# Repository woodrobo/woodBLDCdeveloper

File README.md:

# woodBLDCdeveloper
Prototype BLDC motor driver

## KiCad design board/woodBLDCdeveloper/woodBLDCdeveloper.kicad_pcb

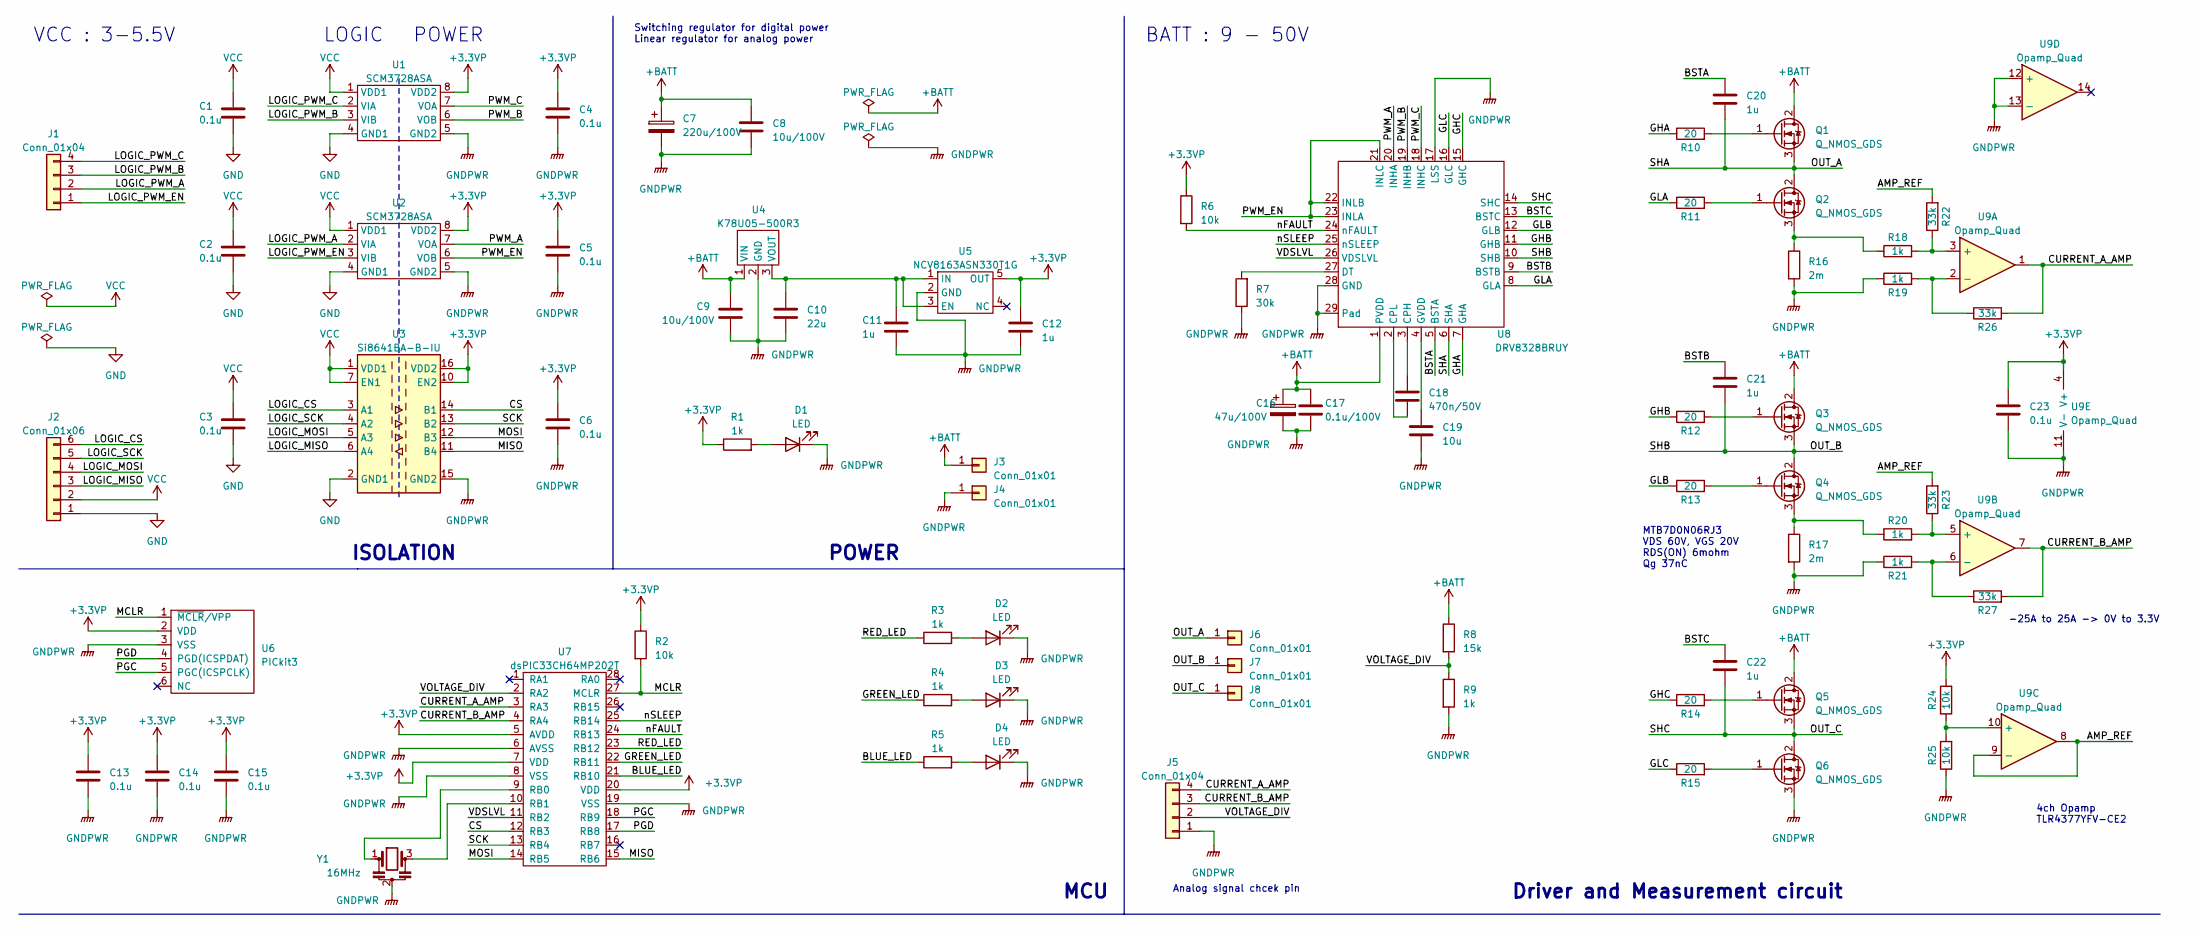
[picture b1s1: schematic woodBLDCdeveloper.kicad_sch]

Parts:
C1, C2, C3, C4, C5, C6, C13, C14, C15, C23: 0.1u; C_0603_1608Metric_Pad1.08x0.95mm_HandSolder
C7: 220u/100V; CP_Radial_D12.5mm_P5.00mm
C8, C9: 10u/100V; C_1210_3225Metric_Pad1.33x2.70mm_HandSolder
C10: 22u; C_0805_2012Metric_Pad1.18x1.45mm_HandSolder
C11, C12, C20, C21, C22: 1u; C_0603_1608Metric_Pad1.08x0.95mm_HandSolder
C16: 47u/100V; CP_Radial_D10.0mm_P5.00mm
C17: 0.1u/100V; C_0603_1608Metric_Pad1.08x0.95mm_HandSolder
C18: 470n/50V; C_0603_1608Metric_Pad1.08x0.95mm_HandSolder
C19: 10u; C_0805_2012Metric_Pad1.18x1.45mm_HandSolder
D1, D2, D3, D4: LED; LED_0603_1608Metric_Pad1.05x0.95mm_HandSolder
J1: Conn_01x04; JST_XH_S4B-XH-A_1x04_P2.50mm_Horizontal
J2: Conn_01x06; JST_XH_S6B-XH-A_1x06_P2.50mm_Horizontal
J3, J4, J6, J7, J8: Conn_01x01; MountingHole_2.2mm_M2_Pad_Via
J5: Conn_01x04; JST_XH_B4B-XH-A_1x04_P2.50mm_Vertical
Q1, Q2, Q3, Q4, Q5, Q6: Q_NMOS_GDS; TO-252-2
R1, R3, R4, R5, R9, R18, R19, R20, R21: 1k; R_0603_1608Metric_Pad0.98x0.95mm_HandSolder
R2, R6, R24, R25: 10k; R_0603_1608Metric_Pad0.98x0.95mm_HandSolder
R7: 30k; R_0603_1608Metric_Pad0.98x0.95mm_HandSolder
R8: 15k; R_0603_1608Metric_Pad0.98x0.95mm_HandSolder
R10, R11, R12, R13, R14, R15: 20; R_0603_1608Metric_Pad0.98x0.95mm_HandSolder
R16, R17: 2m; R_1206_3216Metric_Pad1.30x1.75mm_HandSolder
R22, R23, R26, R27: 33k; R_0603_1608Metric_Pad0.98x0.95mm_HandSolder
U1, U2: SCM3728ASA; SOIC-8_3.9x4.9mm_P1.27mm
U3: Si8641BA-B-IU; QSOP-16_3.9x4.9mm_P0.635mm
U4: K78U05-500R3; K78Uxx-500R3
U5: NCV8163ASN330T1G; TSOP-5_1.65x3.05mm_P0.95mm
U6: PICkit3; PinHeader_1x06_P2.54mm_Horizontal
U7: dsPIC33CH64MP202T; SSOP-28_5.3x10.2mm_P0.65mm
U8: DRV8328BRUY; QFN-28-1EP_4x4mm_P0.4mm_EP2.6x2.6mm
U9: Opamp_Quad; TSSOP-14_4.4x5mm_P0.65mm
Y1: 16MHz; Resonator_SMD_Murata_CSTxExxV-3Pin_3.0x1.1mm

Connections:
+3.3VP: C4.1, C5.1, C6.1, C12.1, C13.1, C14.1, C15.1, C23.1, R1.1, R2.1, R6.1, R24.2, U1.8 (VDD2), U2.8 (VDD2), U3.10 (EN2), U3.16 (VDD2), U5.5 (OUT), U6.2 (VDD), U7.5 (AVDD), U7.7 (VDD), U7.20 (VDD), U9.4 (V+)
+BATT: C7.1, C8.1, C9.1, C16.1, C17.1, J3.1, Q1.2 (D), Q3.2 (D), Q5.2 (D), R8.1, U4.1 (VIN), U8.1 (PVDD)
/AMP_REF: R22.2, R23.2, U9.8, U9.9 (-)
/BLUE_LED: R5.1, U7.21 (RB10)
/BSTA: C20.1, U8.5 (BSTA)
/BSTB: C21.1, U8.9 (BSTB)
/BSTC: C22.1, U8.13 (BSTC)
/CS: U3.14 (B1), U7.12 (RB3)
/CURRENT_A_AMP: J5.4, R26.2, U7.3 (RA3), U9.1
/CURRENT_B_AMP: J5.3, R27.2, U7.4 (RA4), U9.7
/GHA: R10.1, U8.7 (GHA)
/GHB: R12.1, U8.11 (GHB)
/GHC: R14.1, U8.15 (GHC)
/GLA: R11.1, U8.8 (GLA)
/GLB: R13.1, U8.12 (GLB)
/GLC: R15.1, U8.16 (GLC)
/GREEN_LED: R4.1, U7.22 (RB11)
/LOGIC_CS: J2.6, U3.3 (A1)
/LOGIC_MISO: J2.3, U3.6 (A4)
/LOGIC_MOSI: J2.4, U3.5 (A3)
/LOGIC_PWM_A: J1.2, U2.2 (VIA)
/LOGIC_PWM_B: J1.3, U1.3 (VIB)
/LOGIC_PWM_C: J1.4, U1.2 (VIA)
/LOGIC_PWM_EN: J1.1, U2.3 (VIB)
/LOGIC_SCK: J2.5, U3.4 (A2)
/MCLR: R2.2, U6.1 (~MCLR/VPP), U7.27 (MCLR)
/MISO: U3.11 (B4), U7.15 (RB6)
/MOSI: U3.12 (B3), U7.14 (RB5)
/OUT_A: C20.2, J6.1, Q1.3 (S), Q2.2 (D), U8.6 (SHA)
/OUT_B: C21.2, J7.1, Q3.3 (S), Q4.2 (D), U8.10 (SHB)
/OUT_C: C22.2, J8.1, Q5.3 (S), Q6.2 (D), U8.14 (SHC)
/PGC: U6.5 (PGC(ICSPCLK)), U7.18 (RB9)
/PGD: U6.4 (PGD(ICSPDAT)), U7.17 (RB8)
/PWM_A: U2.7 (VOA), U8.20 (INHA)
/PWM_B: U1.6 (VOB), U8.19 (INHB)
/PWM_C: U1.7 (VOA), U8.18 (INHC)
/PWM_EN: U2.6 (VOB), U8.21 (INLC), U8.22 (INLB), U8.23 (INLA)
/RED_LED: R3.1, U7.23 (RB12)
/SCK: U3.13 (B2), U7.13 (RB4)
/VDSLVL: U7.11 (RB2), U8.26 (VDSLVL)
/VOLTAGE_DIV: J5.2, R8.2, R9.1, U7.2 (RA2)
/nFAULT: R6.2, U7.24 (RB13), U8.24 (nFAULT)
/nSLEEP: U7.25 (RB14), U8.25 (nSLEEP)
GND: C1.2, C2.2, C3.2, J2.1, U1.4 (GND1), U2.4 (GND1), U3.2 (GND1), U3.8 (GND1)
GNDPWR: C4.2, C5.2, C6.2, C7.2, C8.2, C9.2, C10.2, C11.2, C12.2, C13.2, C14.2, C15.2, C16.2, C17.2, C19.2, C23.2, D1.1 (K), D2.1 (K), D3.1 (K), D4.1 (K), J4.1, J5.1, Q6.3 (S), R7.1, R9.2, R16.2, R17.2, R19.1, R21.1, R25.1, U1.5 (GND2), U2.5 (GND2), U3.9 (GND2), U3.15 (GND2), U4.2 (GND), U5.2 (GND), U6.3 (VSS), U7.6 (AVSS), U7.8 (VSS), U7.19 (VSS), U8.17 (LSS), U8.28 (GND), U8.29 (Pad), U9.11 (V-), U9.12 (+), U9.13 (-), Y1.2
unnamed: D1.2 (A), R1.2
unnamed: D2.2 (A), R3.2
unnamed: D3.2 (A), R4.2
unnamed: D4.2 (A), R5.2
unnamed: Q1.1 (G), R10.2
unnamed: Q2.1 (G), R11.2
unnamed: Q2.3 (S), R16.1, R18.1
unnamed: Q3.1 (G), R12.2
unnamed: Q4.1 (G), R13.2
unnamed: Q4.3 (S), R17.1, R20.1
unnamed: Q5.1 (G), R14.2
unnamed: Q6.1 (G), R15.2
unnamed: C10.1, C11.1, U4.3 (VOUT), U5.1 (IN), U5.3 (EN)
unnamed: U7.9 (RB0), Y1.1
unnamed: U7.10 (RB1), Y1.3
unnamed: C18.1, U8.3 (CPH)
unnamed: C18.2, U8.2 (CPL)
unnamed: R7.2, U8.27 (DT)
unnamed: C19.1, U8.4 (GVDD)
unnamed: R18.2, R22.1, U9.3 (+)
unnamed: R19.2, R26.1, U9.2 (-)
unnamed: R20.2, R23.1, U9.5 (+)
unnamed: R21.2, R27.1, U9.6 (-)
unnamed: R24.1, R25.2, U9.10 (+)
VCC: C1.1, C2.1, C3.1, J2.2, U1.1 (VDD1), U2.1 (VDD1), U3.1 (VDD1), U3.7 (EN1)

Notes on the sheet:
Analog signal chcek pin
MTB7D0N06RJ3 VDS 60V, VGS 20V RDS(ON) 6mohm Qg 37nC
POWER
Switching regulator for digital power Linear regulator for analog power
VCC : 3-5.5V
BATT : 9 - 50V
-25A to 25A -> 0V to 3.3V
ISOLATION
MCU
4ch Opamp TLR4377YFV-CE2
Driver and Measurement circuit
LOGIC

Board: 2 copper layers, 78 parts (0 on the bottom side), 70 nets, no tracks yet.

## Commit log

2023-03-31 回路図完成
2023-04-01 回路設計と部品割り当て終わった
